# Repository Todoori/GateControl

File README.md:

# PCBProjectTemplate
Use this Repository as a Template to start your PCB Project. It contatins the general structure that should be used.
You can also add Images and [links](https://www.youtube.com/watch?v=dQw4w9WgXcQ) if needed. 

## Assembly Instructions
- Do not solder those parts
- solder this solder bridge
- Do not soldet that solder bridge
- Use this part for R_example
- Be extra careful soldering this and that
- Do not aply to much heat to this part
- 
- 
- 

## Usage Instructions
- Try not to tuch this when PCB is on
- Use this software for programing that IC
- Here are some measurement Points
- 
- 
- 

## Additional Information

Feel free to add Information that you thing might be useful.

e.g. how a IC is connected on your Board:
### Pinout on Board

| PICO GPIO PIN  | Connected to |
| -------------  | ------------- |
| 0  |           |*|
| 1  |           INT (CAN)|
| 2  |           SPI0 SCK (CAN)|
| 3  |           SPI0 TX (MOSI on Pico) (CAN)|
| 4  |           SPI0 RX (MISO on Pico) (CAN)|
| 5  |           SPIO0 CS (CAN)|
| 6  |           LED Fault|
| 7  |           |*|
| 8  |           D7|
| 9  |           D8|
| 10  |          D9|
| 11  |          D10|
| 12  |          SPI1 RX (ADC)|
| 13  |          SPI1 CS (ADC)|
| 14  |          SPI1 SCK (ADC)|
| 15  |          SPI1 TX (ADC)|
| 16  |          D5|
| 17  |          D6|
| 18  |          D3|
| 19  |          D4|
| 20  |          D1|
| 21  |          D2|
| 22  |          |*|
| 23  |          |*|
| 24  |          |*|
| 25  |          |*|
| 26  |          A1|
| 27  |          A2|
| 28  |          SHUNT_ADC|

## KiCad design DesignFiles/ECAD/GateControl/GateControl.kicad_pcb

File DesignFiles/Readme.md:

# This is a place for your Altium files

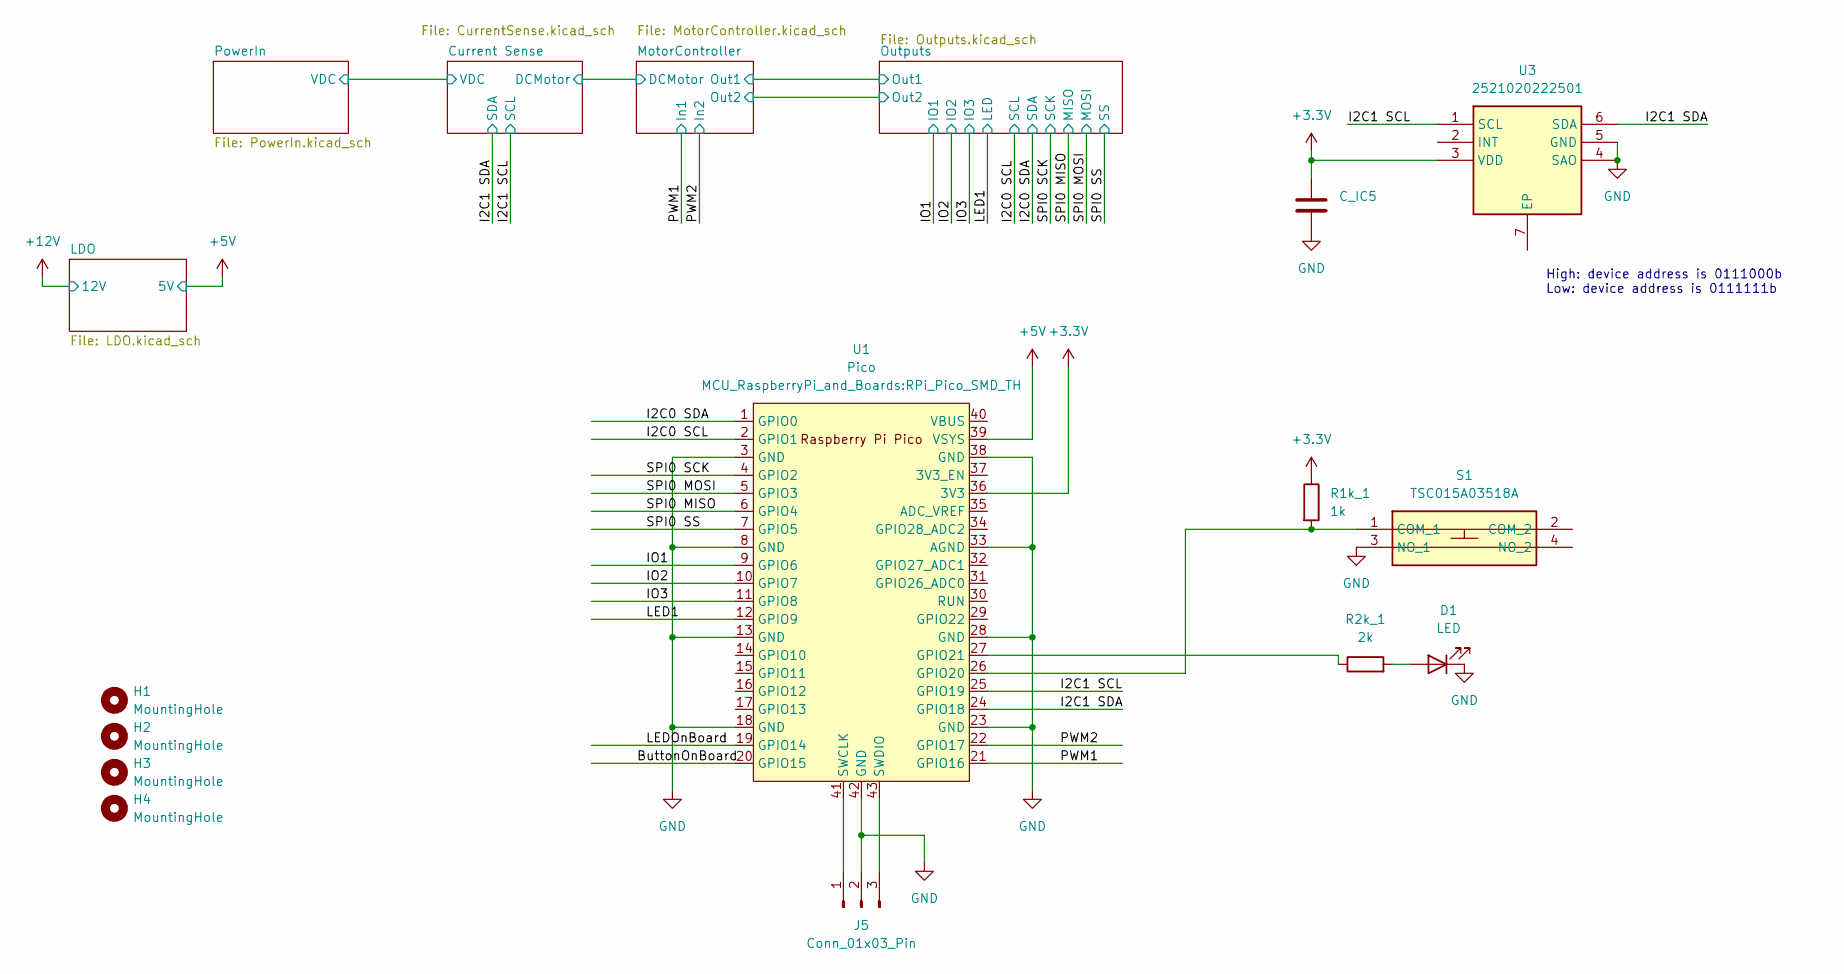
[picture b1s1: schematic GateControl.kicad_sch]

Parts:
C_IC5: C_Disc_D5.0mm_W2.5mm_P5.00mm
D1: LED; LED_0603_1608Metric_Pad1.05x0.95mm_HandSolder
H1, H2, H3, H4: MountingHole; MountingHole_3.2mm_M3_DIN965
J5: Conn_01x03_Pin; PinSocket_1x03_P2.54mm_Vertical
R1k_1: 1k; R_Axial_DIN0207_L6.3mm_D2.5mm_P7.62mm_Horizontal
R2k_1: 2k; R_0805_2012Metric_Pad1.20x1.40mm_HandSolder
S1: TSC015A03518A; Manufacturer_Part_Number TSC015A03518A
U1: Pico; RPi_Pico_SMD_TH
U3: 2521020222501; SON65P200X200X55-7N-D; Manufacturer_Part_Number 2521020222501; Mouser Part Number 710-2521020222501

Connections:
+3.3V: C_IC5.1, R1k_1.1, U1.36 (3V3), U3.3 (VDD); also elsewhere on the board
+5V: U1.39 (VSYS); also elsewhere on the board
/ButtonOnBoard: U1.20 (GPIO15)
/I2C0 SCL: U1.2 (GPIO1); also elsewhere on the board
/I2C0 SDA: U1.1 (GPIO0); also elsewhere on the board
/I2C1 SCL: U1.25 (GPIO19), U3.1 (SCL); also elsewhere on the board
/I2C1 SDA: U1.24 (GPIO18), U3.6 (SDA); also elsewhere on the board
/IO1: U1.9 (GPIO6); also elsewhere on the board
/IO2: U1.10 (GPIO7); also elsewhere on the board
/IO3: U1.11 (GPIO8); also elsewhere on the board
/LED1: U1.12 (GPIO9); also elsewhere on the board
/LEDOnBoard: U1.19 (GPIO14)
/PWM1: U1.21 (GPIO16); also elsewhere on the board
/PWM2: U1.22 (GPIO17); also elsewhere on the board
/SPI0 MISO: U1.6 (GPIO4); also elsewhere on the board
/SPI0 MOSI: U1.5 (GPIO3); also elsewhere on the board
/SPI0 SCK: U1.4 (GPIO2); also elsewhere on the board
/SPI0 SS: U1.7 (GPIO5); also elsewhere on the board
GND: C_IC5.2, D1.1 (K), J5.2, S1.3 (NO_1), U1.3 (GND), U1.8 (GND), U1.13 (GND), U1.18 (GND), U1.23 (GND), U1.28 (GND), U1.33 (AGND), U1.38 (GND), U1.42 (GND), U3.4 (SAO), U3.5 (GND); also elsewhere on the board
unnamed: D1.2 (A), R2k_1.2
unnamed: J5.1, U1.41 (SWCLK)
unnamed: J5.3, U1.43 (SWDIO)
unnamed: R1k_1.2, S1.1 (COM_1), U1.26 (GPIO20)
unnamed: R2k_1.1, U1.27 (GPIO21)

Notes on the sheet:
High: device address is 0111000b Low: device address is 0111111b

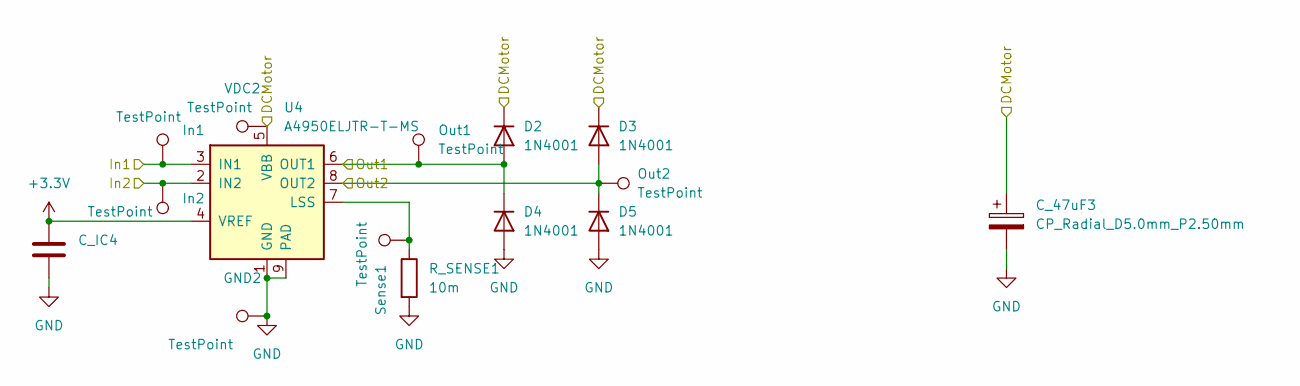
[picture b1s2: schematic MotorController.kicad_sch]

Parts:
C_47uF3: CP_Radial_D5.0mm_P2.50mm
C_IC4: C_Disc_D5.0mm_W2.5mm_P5.00mm
D2, D3, D4, D5: 1N4001; D_DO-41_SOD81_P10.16mm_Horizontal
GND2: TestPoint; TestPoint_THTPad_1.0x1.0mm_Drill0.5mm
In1, In2: TestPoint; TestPoint_THTPad_1.0x1.0mm_Drill0.5mm
Out1, Out2: TestPoint; TestPoint_THTPad_1.0x1.0mm_Drill0.5mm
R_SENSE1: 10m; R_1206_3216Metric_Pad1.30x1.75mm_HandSolder; Mfr. Part RTT06R010FTP
Sense1: TestPoint; TestPoint_THTPad_1.0x1.0mm_Drill0.5mm
U4: A4950ELJTR-T-MS; SOIC8
VDC2: TestPoint; TestPoint_THTPad_1.0x1.0mm_Drill0.5mm

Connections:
+3.3V: C_IC4.1, U4.4 (VREF); also elsewhere on the board
/Current Sense/DCMotor: C_47uF3.1, D2.1 (K), D3.1 (K), U4.5 (VBB), VDC2.1; also elsewhere on the board
/MotorController/Out1: D2.2 (A), D4.1 (K), Out1.1, U4.6 (OUT1); also elsewhere on the board
/MotorController/Out2: D3.2 (A), D5.1 (K), Out2.1, U4.8 (OUT2); also elsewhere on the board
/PWM1: In1.1, U4.3 (IN1); also elsewhere on the board
/PWM2: In2.1, U4.2 (IN2); also elsewhere on the board
GND: C_47uF3.2, C_IC4.2, D4.2 (A), D5.2 (A), GND2.1, R_SENSE1.2, U4.1 (GND), U4.9 (PAD); also elsewhere on the board
unnamed: R_SENSE1.1, Sense1.1, U4.7 (LSS)

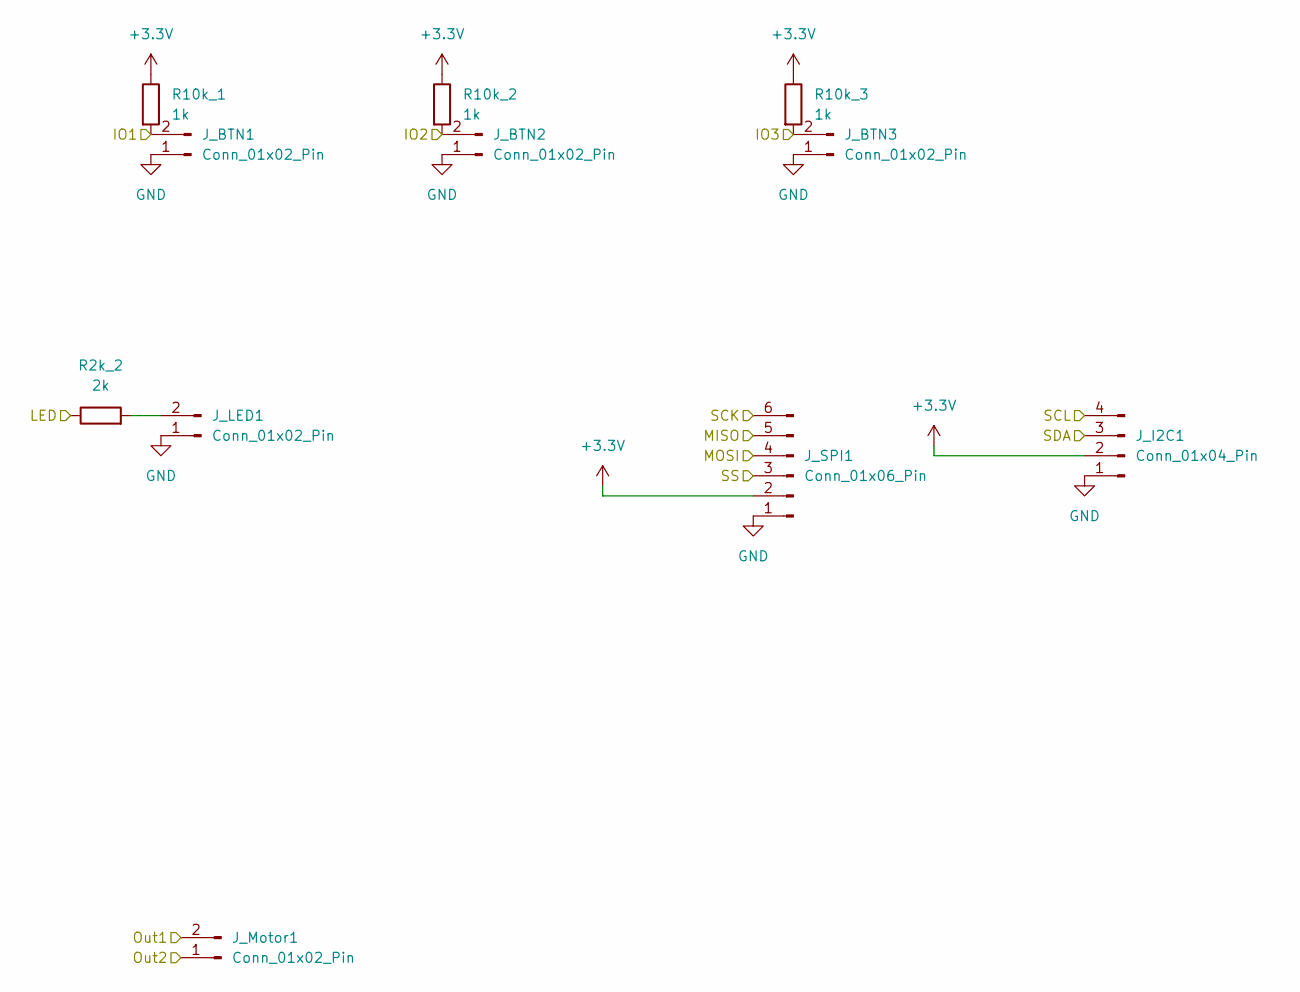
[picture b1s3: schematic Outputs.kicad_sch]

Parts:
J_BTN1, J_BTN2, J_BTN3: Conn_01x02_Pin; JST_XH_B2B-XH-A_1x02_P2.50mm_Vertical
J_I2C1: Conn_01x04_Pin; JST_XH_B4B-XH-A_1x04_P2.50mm_Vertical
J_LED1: Conn_01x02_Pin; JST_XH_B2B-XH-A_1x02_P2.50mm_Vertical
J_Motor1: Conn_01x02_Pin; JST_XH_B2B-XH-A_1x02_P2.50mm_Vertical
J_SPI1: Conn_01x06_Pin; JST_XH_B6B-XH-A_1x06_P2.50mm_Vertical
R2k_2: 2k; R_Axial_DIN0207_L6.3mm_D2.5mm_P7.62mm_Horizontal
R10k_1, R10k_2, R10k_3: 1k; R_Axial_DIN0207_L6.3mm_D2.5mm_P7.62mm_Horizontal

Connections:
+3.3V: J_I2C1.2, J_SPI1.2, R10k_1.1, R10k_2.1, R10k_3.1; also elsewhere on the board
/I2C0 SCL: J_I2C1.4; also elsewhere on the board
/I2C0 SDA: J_I2C1.3; also elsewhere on the board
/IO1: J_BTN1.2, R10k_1.2; also elsewhere on the board
/IO2: J_BTN2.2, R10k_2.2; also elsewhere on the board
/IO3: J_BTN3.2, R10k_3.2; also elsewhere on the board
/LED1: R2k_2.1; also elsewhere on the board
/MotorController/Out1: J_Motor1.2; also elsewhere on the board
/MotorController/Out2: J_Motor1.1; also elsewhere on the board
/SPI0 MISO: J_SPI1.5; also elsewhere on the board
/SPI0 MOSI: J_SPI1.4; also elsewhere on the board
/SPI0 SCK: J_SPI1.6; also elsewhere on the board
/SPI0 SS: J_SPI1.3; also elsewhere on the board
GND: J_BTN1.1, J_BTN2.1, J_BTN3.1, J_I2C1.1, J_LED1.1, J_SPI1.1; also elsewhere on the board
unnamed: J_LED1.2, R2k_2.2

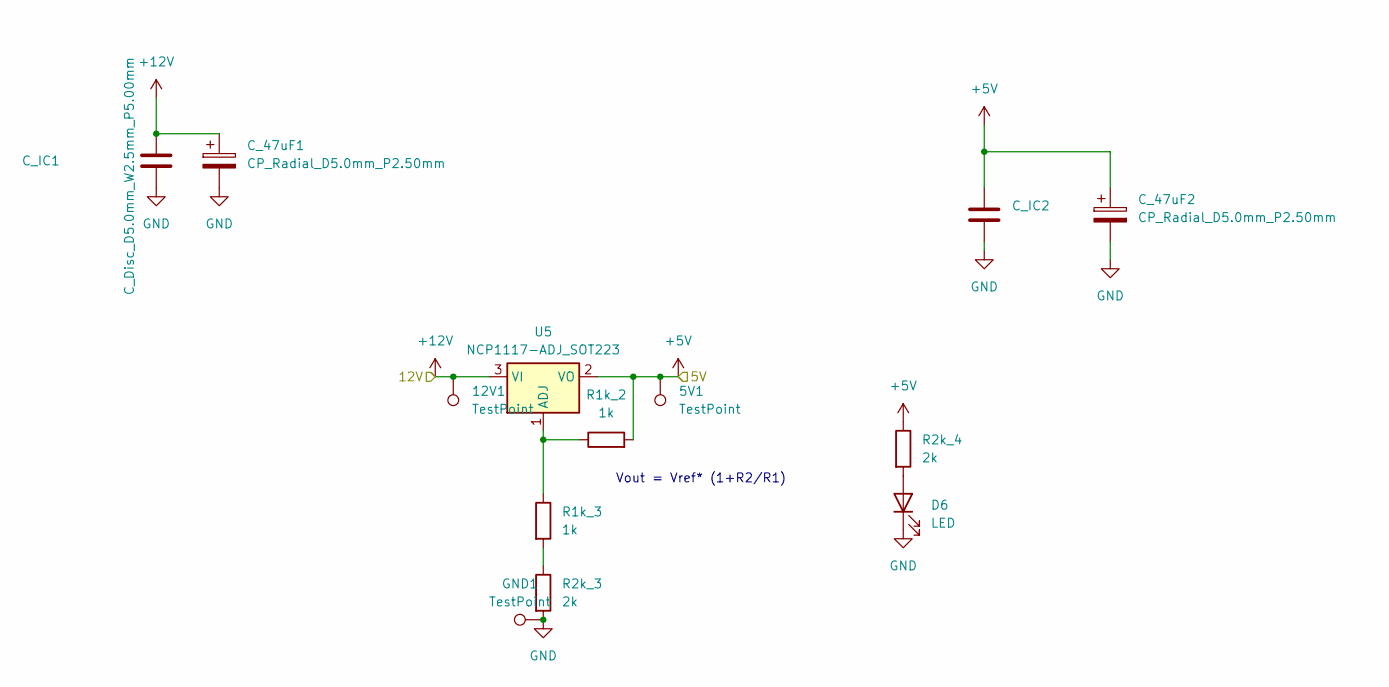
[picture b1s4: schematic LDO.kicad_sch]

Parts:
5V1, 12V1: TestPoint; TestPoint_THTPad_1.0x1.0mm_Drill0.5mm
C_47uF1, C_47uF2: CP_Radial_D5.0mm_P2.50mm
C_IC1, C_IC2: C_Disc_D5.0mm_W2.5mm_P5.00mm
D6: LED; LED_0603_1608Metric_Pad1.05x0.95mm_HandSolder
GND1: TestPoint; TestPoint_THTPad_1.0x1.0mm_Drill0.5mm
R1k_2, R1k_3: 1k; R_Axial_DIN0207_L6.3mm_D2.5mm_P7.62mm_Horizontal
R2k_3: 2k; R_Axial_DIN0207_L6.3mm_D2.5mm_P7.62mm_Horizontal
R2k_4: 2k; R_0805_2012Metric_Pad1.20x1.40mm_HandSolder
U5: NCP1117-ADJ_SOT223; SOT-223-3_TabPin2

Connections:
+5V: 5V1.1, C_47uF2.1, C_IC2.1, R1k_2.2, R2k_4.1, U5.2 (VO); also elsewhere on the board
+12V: 12V1.1, C_47uF1.1, C_IC1.1, U5.3 (VI); also elsewhere on the board
GND: C_47uF1.2, C_47uF2.2, C_IC1.2, C_IC2.2, D6.1 (K), GND1.1, R2k_3.2; also elsewhere on the board
unnamed: D6.2 (A), R2k_4.2
unnamed: R1k_3.2, R2k_3.1
unnamed: R1k_2.1, R1k_3.1, U5.1 (ADJ)

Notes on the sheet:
Vout = Vref* (1+R2/R1)

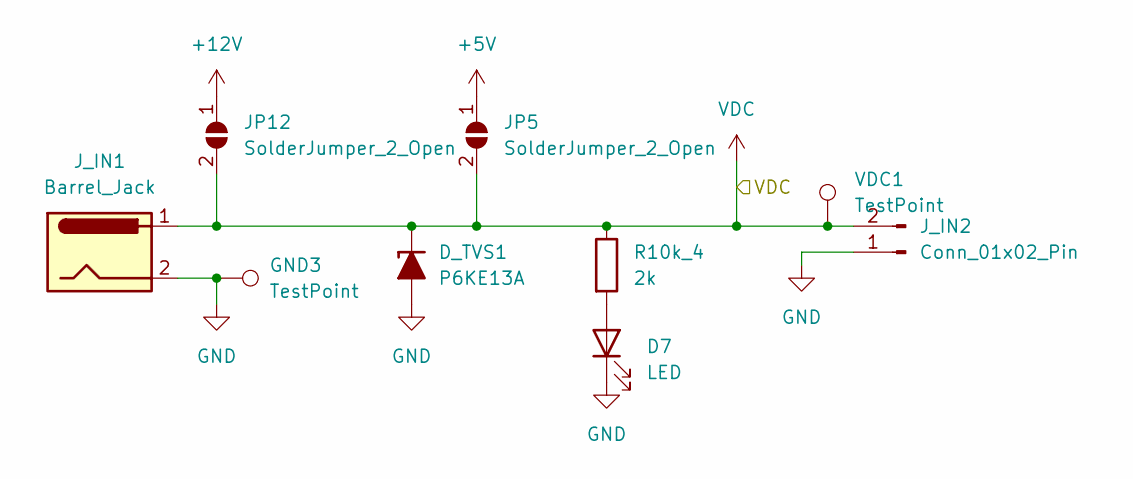
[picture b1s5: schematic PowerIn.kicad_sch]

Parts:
D7: LED; LED_0603_1608Metric_Pad1.05x0.95mm_HandSolder
D_TVS1: P6KE13A; D_DO-15_P5.08mm_Vertical_KathodeUp
GND3: TestPoint; TestPoint_THTPad_1.0x1.0mm_Drill0.5mm
JP5, JP12: SolderJumper_2_Open; SolderJumper-2_P1.3mm_Open_RoundedPad1.0x1.5mm
J_IN1: Barrel_Jack; BarrelJack_2,inner_5,5outer_DC-005 2.0
J_IN2: Conn_01x02_Pin; JST_XH_B2B-XH-A_1x02_P2.50mm_Vertical
R10k_4: 2k; R_0805_2012Metric_Pad1.20x1.40mm_HandSolder
VDC1: TestPoint; TestPoint_THTPad_1.0x1.0mm_Drill0.5mm

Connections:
+5V: JP5.1 (A); also elsewhere on the board
+12V: JP12.1 (A); also elsewhere on the board
GND: D7.1 (K), D_TVS1.2 (A), GND3.1, J_IN1.2, J_IN2.1; also elsewhere on the board
unnamed: D7.2 (A), R10k_4.2
VDC: D_TVS1.1 (K), JP5.2 (B), JP12.2 (B), J_IN1.1, J_IN2.2, R10k_4.1, VDC1.1; also elsewhere on the board

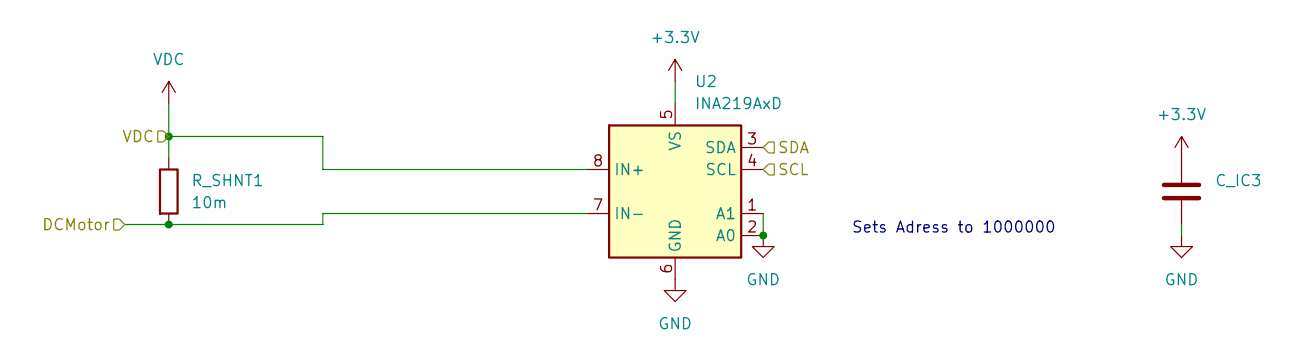
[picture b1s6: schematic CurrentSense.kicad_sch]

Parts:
C_IC3: C_Disc_D5.0mm_W2.5mm_P5.00mm
R_SHNT1: 10m; R_1206_3216Metric_Pad1.30x1.75mm_HandSolder; Mfr. Part RTT06R010FTP
U2: INA219AxD; SOIC-8_3.9x4.9mm_P1.27mm

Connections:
+3.3V: C_IC3.1, U2.5 (VS); also elsewhere on the board
/Current Sense/DCMotor: R_SHNT1.2, U2.7 (IN-); also elsewhere on the board
/I2C1 SCL: U2.4 (SCL); also elsewhere on the board
/I2C1 SDA: U2.3 (SDA); also elsewhere on the board
GND: C_IC3.2, U2.1 (A1), U2.2 (A0), U2.6 (GND); also elsewhere on the board
VDC: R_SHNT1.1, U2.8 (IN+); also elsewhere on the board

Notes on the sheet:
Sets Adress to 1000000

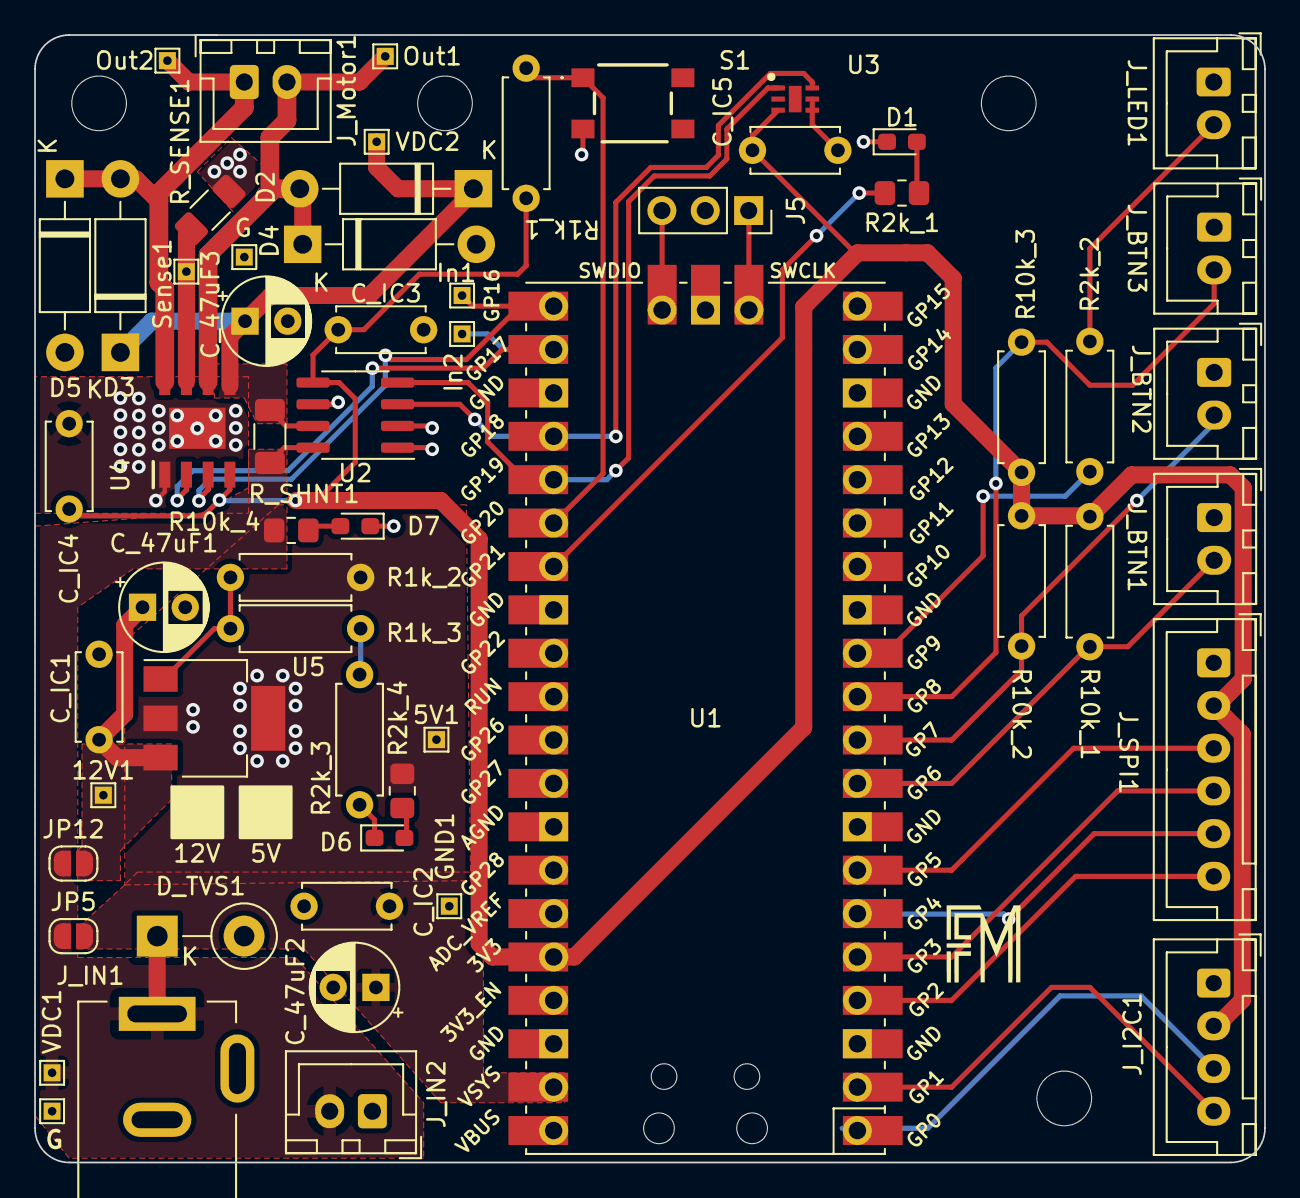
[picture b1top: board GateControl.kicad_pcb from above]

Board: 2 copper layers, 72.0 x 66.0 mm, 63 parts (0 on the bottom side), 33 nets.

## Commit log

2023-12-31 updated diagramm
2024-01-01 finished shematic, started PCB Layout
2024-01-02 finished PCB
2024-01-27 software projekt
